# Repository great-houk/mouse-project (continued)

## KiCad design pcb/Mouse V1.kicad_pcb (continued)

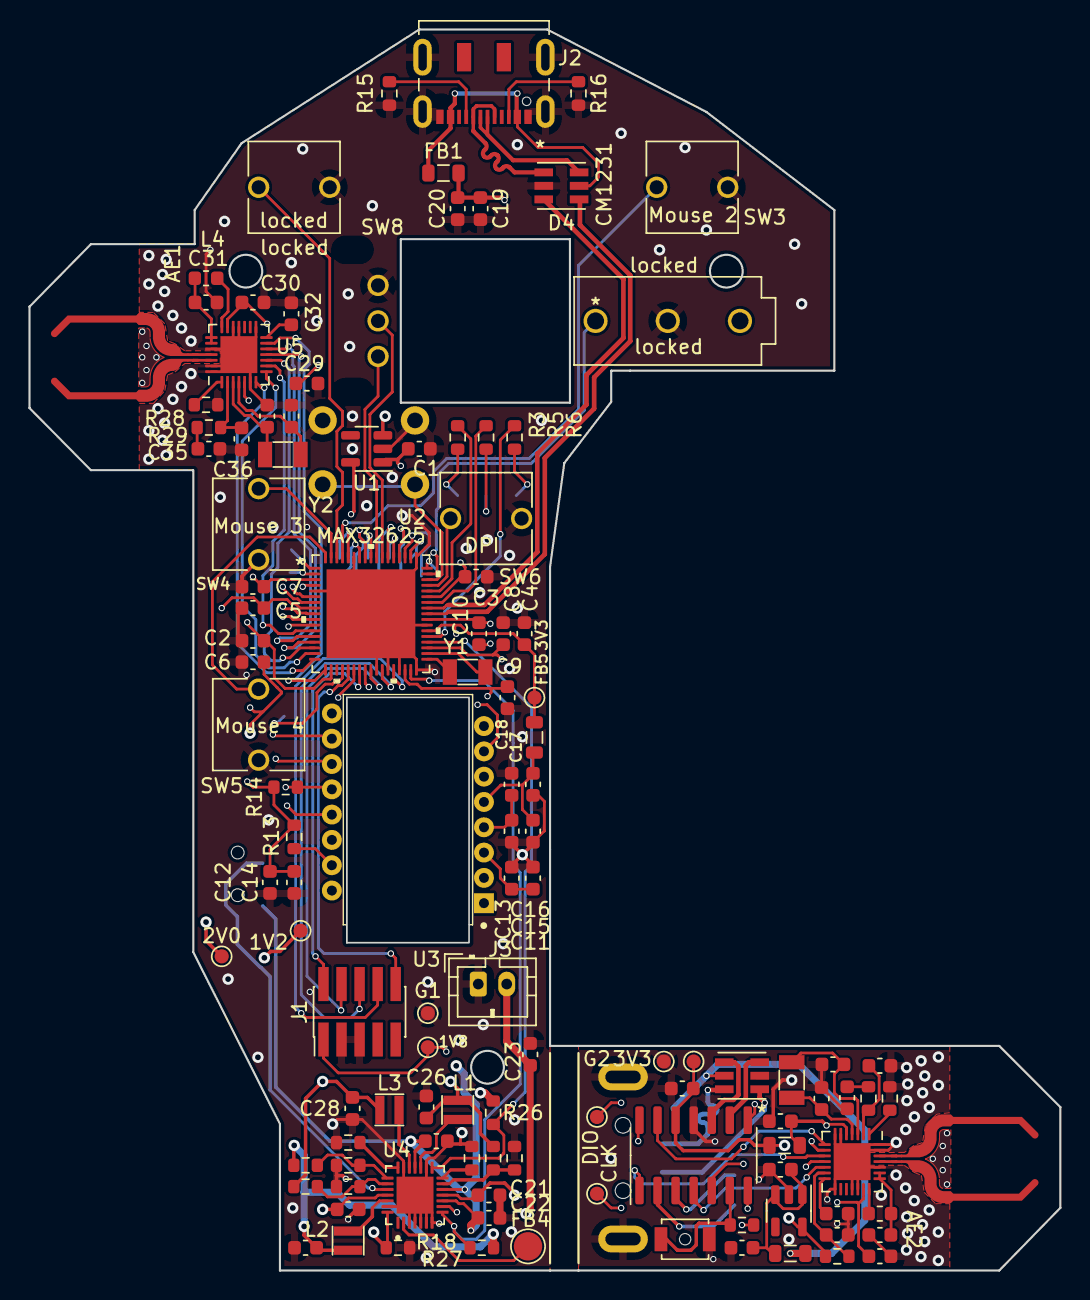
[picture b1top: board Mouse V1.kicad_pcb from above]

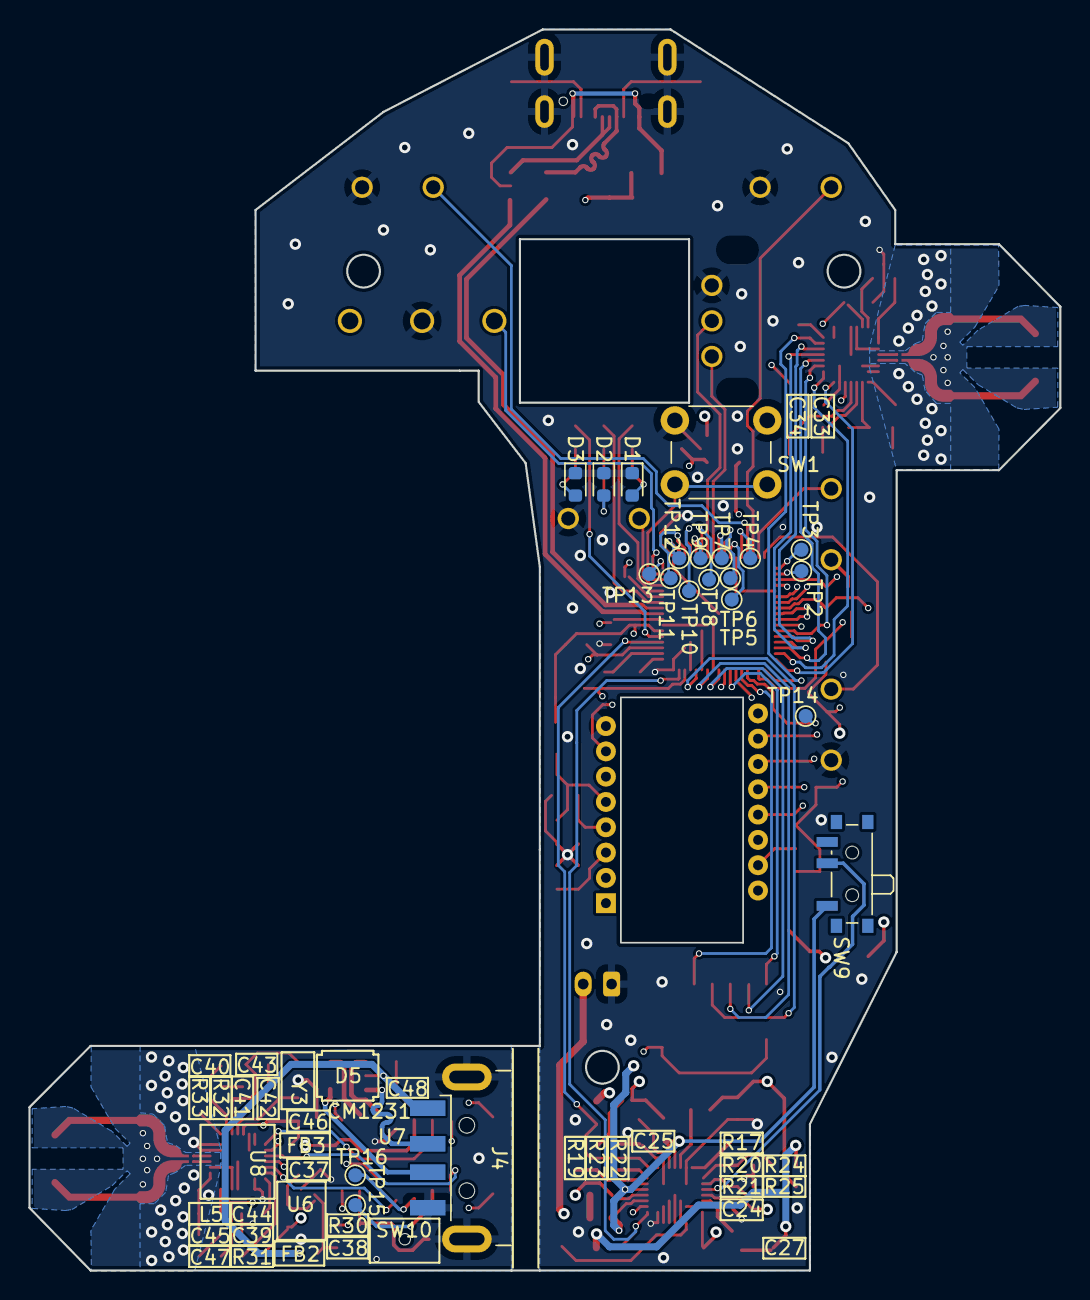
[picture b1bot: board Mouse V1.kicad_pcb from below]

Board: 4 copper layers, 72.5 x 87.3 mm, 138 parts (21 on the bottom side), 117 nets.

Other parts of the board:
3V3#2: 3.3V Test Point; TestPoint_Pad_D1.0mm
CLK: TestPoint; TestPoint_Pad_D1.0mm
DIO: TestPoint; TestPoint_Pad_D1.0mm
locked: locked; D2F-01L
locked#2: locked; TL59AF100Q

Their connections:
/Microprocessor/Mouse Button 1: locked#2.1; also elsewhere on the board
/Microprocessor/Mouse Scroll Click: locked.1; also elsewhere on the board
GND: locked.2, locked#2.2; also elsewhere on the board
unnamed 41: 3V3#2.1; also elsewhere on the board
unnamed 64: CLK.1; also elsewhere on the board
unnamed 76: DIO.1; also elsewhere on the board

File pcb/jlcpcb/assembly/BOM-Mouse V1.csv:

Comment,Designator,Footprint,LCSC
4.7uH,"L1,L2,L3",L_Taiyo-Yuden_MD-2020,C574030
390K +- 5%,R29,R_0603_1608Metric,
FBMJ2125HS250NT,FB1,L_0805_2012Metric,
68pF C0G NP0,C36,C_0603_1608Metric,
10uF 10V,C37,C_0603_1608Metric,
2.2M +- 1%,R28,R_0603_1608Metric,
GRPB052VWQS-RC,J1,PinHeader_2x05_P1.27mm_Vertical_SMD,
10uF 10V,C26,C_0603_1608Metric,
10K,R14,R_0603_1608Metric,
4.7uF 10V,C11,C_0603_1608Metric,
1uF,C29,C_0603_1608Metric,
ABS07-120-32.768KHZ-T,Y2,Crystal_SMD_3215-2Pin_3.2x1.5mm,
1M,R17,R_0603_1608Metric,
SR1020-28QFN-TR,U5,QFN-28-1EP_4x4mm_P0.4mm_EP2.6x2.6mm,
10pF,C34,C_0603_1608Metric,
MAX8819CETI+,U4,QFN40P400X400X80-29N,
1M,R18,R_0603_1608Metric,
100K,R21,R_0603_1608Metric,
120K,R23,R_0603_1608Metric,
10uF 10V,C22,C_0603_1608Metric,
100K,R20,R_0603_1608Metric,
2.2uF,C24,C_0603_1608Metric,
100nF 10V,C13,C_0603_1608Metric,
10uF 10V,C12,C_0603_1608Metric,
10uF 10V,C16,C_0603_1608Metric,
180nH,L4,L_0603_1608Metric,
1uF,C31,C_0603_1608Metric,
100nF 10V,C14,C_0603_1608Metric,
10uF 10V,C19,C_0603_1608Metric,
100nF 10V,C15,C_0603_1608Metric,
470K,R26,R_0603_1608Metric,
100K,R19,R_0603_1608Metric,
10uF 10V,C17,C_0603_1608Metric,
80.6K,R24,R_0603_1608Metric,
1uF,C10,C_0603_1608Metric,
1uF,C30,C_0603_1608Metric,
13,R13,R_0603_1608Metric,
100nF 10V,C32,C_0603_1608Metric,
4.7uF 10V,C23,C_0603_1608Metric,
MAX32625,U2,MAX32625ITKL&plus_,
4.7uF 10V,C25,C_0603_1608Metric,
10uF 10V,C28,C_0603_1608Metric,
680pF C0G NP0,C35,C_0603_1608Metric,
470K,R27,R_0603_1608Metric,
20K,R25,R_0603_1608Metric,
3K,R22,R_0603_1608Metric,
10uF 10V,C27,C_0603_1608Metric,
100nF 10V,C18,C_0603_1608Metric,
10pF,C33,C_0603_1608Metric,
1uF,C8,C_0603_1608Metric,
200,R6,R_0603_1608Metric,
LED,D2,LED_0603_1608Metric,
1uF,C2,C_0603_1608Metric,
5.1K,R16,R_0603_1608Metric,
LED,D3,LED_0603_1608Metric,
5.1K,R15,R_0603_1608Metric,
1uF,C7,C_0603_1608Metric,
1uF,C4,C_0603_1608Metric,
2137160001,J2,USB_C_Receptacle_JAE_DX07S016JA1R1500,
200,R5,R_0603_1608Metric,
1uF,C1,C_0603_1608Metric,
1uF,C6,C_0603_1608Metric,
ABS07-120-32.768KHZ-T,Y1,Crystal_SMD_3215-2Pin_3.2x1.5mm,
LED,D1,LED_0603_1608Metric,
1uF,C3,C_0603_1608Metric,
S-1740C33-M5T1U4,U1,TSOT-23-5,
1uF,C9,C_0603_1608Metric,
200,R3,R_0603_1608Metric,
1uF,C5,C_0603_1608Metric,
100nF 10V,C20,C_0603_1608Metric,
SW_Push,SW10,SW_SPST_B3U-1000P-B,
1001-011-01101,J4,USB_A_CNCTech_1001-011-01101_Horizontal,
1uF,C48,C_0603_1608Metric,
ABS07-120-32.768KHZ-T,Y3,Crystal_SMD_3215-2Pin_3.2x1.5mm,
SR1020-28QFN-TR,U8,QFN-28-1EP_4x4mm_P0.4mm_EP2.6x2.6mm,
ATSAMD11C14A-SS,U7,SOIC-14_3.9x8.7mm_P1.27mm,
S-1740C33-M5T1U4,U6,TSOT-23-5,
2.2M +- 1%,R33,R_0603_1608Metric,
390K +- 5%,R32,R_0603_1608Metric,
390K +- 5%,R31,R_0603_1608Metric,
100K,R30,R_0603_1608Metric,
180nH,L5,L_0603_1608Metric,
FBMJ2125HS250NT,FB3,L_0805_2012Metric,
FBMJ2125HS250NT,FB2,L_0805_2012Metric,
CM1231,D5,CM1231-02SO,
1uF,C47,C_0603_1608Metric,
1uF,C46,C_0603_1608Metric,
1uF,C45,C_0603_1608Metric,
100nF 10V,C44,C_0603_1608Metric,
10pF,C43,C_0603_1608Metric,
10pF,C42,C_0603_1608Metric,
680pF C0G NP0,C41,C_0603_1608Metric,
68pF C0G NP0,C40,C_0603_1608Metric,
100nF 10V,C39,C_0603_1608Metric,
100nF 10V,C38,C_0603_1608Metric,
4.7uF 10V,C21,C_0603_1608Metric,
CM1231,D4,CM1231-02SO,
FBMJ2125HS250NT,FB5,L_0805_2012Metric,

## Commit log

2022-07-21 Fix lints in mouse
2022-07-21 Made progress on key parsing, untested
2022-07-22 Finished work on key updating, and lints/bugs
2022-07-22 Updated some mouse organization
2022-07-23 Fixed some lints, plus some work on lifting
2022-07-23 Got lifting working + re-factored/worked mouse.rs
2022-07-24 Added battery level, polished commands
2022-07-24 Reworked sensor library, now much better
2022-07-27 Making progress on sensor images
2022-07-28 Got sensor output working!
2022-07-29 Got sensor images working fully :)
2022-07-29 oops lol, included a random file
2022-07-29 Added PCB
2022-07-29 Minor changes to CLI
2022-08-11 Made the mouse more standard, not working
2022-08-14 some more progress, doesn't work fully
2022-08-14 Increased Compatibility (dinput8.dll)
2022-08-14 Made sensor imaging commands more intuitive
2022-08-16 Create LICENSE
2022-12-25 New ommands for sensor lift calibration and dist
2022-12-25 Add license
